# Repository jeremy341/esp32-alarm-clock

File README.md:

# ESP32-S3 Alarm Clock

Custom alarm clock built around an `ESP32-S3-WROOM-1` on a dedicated PCB, with an `ILI9341` display, battery powerer , Website , and USB C for both flashing and charging. The website allows the user to choose from existing presets and change the color of them, to change the UI.
I created this Project as a birthday gift for my little sister as in the morning i always wake her up and she doesnt have a alarm, I also wanted to gain new skills as i want to become an enginier and build up my CV.

## Overview

- `ESP32-S3-WROOM-1`
- `ILI9341` SPI display
- `IP5306` power-path, Li-ion charge, and boost stage
- `LV75533PDBVR` 3.3 V regulator
- `USBLC6-2SC6` USB ESD protection
- `2N3904` transistor-driven buzzer stage with `1N4148`
- `LittleFS` storage for presets and alarms
- `WebSerial` browser app for preset upload

## IMAGES

## Hardware

| Block | Part | Role |
|---|---|---|
| MCU | `ESP32-S3-WROOM-1` | Main control, USB serial, UI logic |
| Display | `ILI9341` | TFT clock UI |
| USB | USB-C receptacle | Power + USB data |
| ESD | `USBLC6-2SC6` | Protection for `D+` / `D-` |
| Power manager | `IP5306` | Li-ion charging and 5 V boost |
| 3.3 V rail | `LV75533PDBVR` | Logic supply for ESP32-S3 and display |
| Audio driver | `2N3904` + `1N4148` | GPIO-switched buzzer stage |
| Storage | `LittleFS` | Preset and alarm persistence |

## Power Path

```text
USB-C VBUS
  -> IP5306
     -> Li-ion charging
     -> 5V_SYS
        -> LV75533PDBVR
           -> 3.3V rail
              -> ESP32-S3 + ILI9341 + logic
```

## Pin Map

### ILI9341

| Signal | GPIO |
|---|---|
| `SCK` | `GPIO12` |
| `MOSI` | `GPIO11` |
| `MISO` | `GPIO13` |
| `CS` | `GPIO10` |
| `DC` | `GPIO9` |
| `RST` | `GPIO14` |
| `GND` | `GND` |
| `VCC` | `3.3V` |

### Buttons

| Function | GPIO | Notes |
|---|---|---|
| `RESET` | `EN` | Active low |
| `BOOT` | `GPIO0` | Hold low during reset for flash mode |
| `MENU` | `GPIO1` | `INPUT_PULLUP`, switch to GND |
| `UP` | `GPIO2` | `INPUT_PULLUP`, switch to GND |
| `DOWN` | `GPIO5` | `INPUT_PULLUP`, switch to GND |

### Other PINS

| Signal | GPIO | Notes |
|---|---|---|
| `BUZZER` | `GPIO4` | Drives transistor stage |
| `USB D-` | `GPIO19` | USB only |
| `USB D+` | `GPIO20` | USB only |

## Web App

The browser app is served from `web/` and is intended for Chrome or firefox, browsers with WebSerial support. Its function is choosing of custom ui and flashing `ESP32`.

## Getting Started

```bash
cd firmware
pio run
pio run -t upload
pio run -t uploadfs
```

```bash
cd web
python -m http.server 8000
```

Then open [http://localhost:8000](http://localhost:8000) in Chrome or Edge.

## Bill of Materials (BOM)

| Part Name | Distributor | Qty | LCSC Part # / Spec | Link | Price |
| :--- | :--- | :--- | :--- | :--- | :--- |
| **ESP32-S3-WROOM-1** | LCSC | 1 | C2913202 | [Link](https://www.lcsc.com/product-detail/C2913202.html) | $4.95 |
| **IP5306** | LCSC | 1 | C181552 | [Link](https://www.lcsc.com/product-detail/C181552.html) | $3.95 |
| **ILI9341 Display** | Aliexpress | 1 | 2.8" SPI TFT | [Link](https://de.aliexpress.com/item/1005009761383945.html) | $5.79 |
| **3000 mAh LiPo Battery** | Aliexpress | 1 | 3.7V Cell | [Link](https://de.aliexpress.com/item/1005009240348340.html) | $14.99 |
| **Custom PCB** | JLCPCB | 1 | 2-Layer FR4 | [Link](https://jlcpcb.com/) | $6.40 |
| **Mechanical Switch (UP)** | Aliexpress | 1 | Gateron/Akko Style | [Link](https://de.aliexpress.com/item/1005011838889689.html) | $0.00* |
| **Mechanical Switch (DOWN)** | Aliexpress | 1 | Gateron/Akko Style | [Link](https://de.aliexpress.com/item/1005011838889689.html) | $2.73 |
| **Mechanical Switch (Menu)** | Aliexpress | 1 | Gateron/Akko Style | [Link](https://de.aliexpress.com/item/1005011838889689.html) | $0.00* |
| **TLV75533PDBV** | LCSC | 1 | C404027 | [Link](https://www.lcsc.com/product-detail/C404027.html) | $0.62 |
| **USBLC6-2SC6** | LCSC | 1 | C7519 | [Link](https://www.lcsc.com/product-detail/C7519.html) | $0.76 |
| **USB-C Port (16P)** | LCSC | 1 | C165948 | [Link](https://www.lcsc.com/product-detail/C165948.html) | $0.85 |
| **Passive Buzzer** | LCSC | 1 | C409842 | [Link](https://www.lcsc.com/product-detail/C409842.html) | $0.71 |
| **Battery Connector** | LCSC | 1 | C22360303 | [Link](https://www.lcsc.com/product-detail/C22360303.html) | $0.35 |
| **2N3904 Transistor** | LCSC | 1 | C2874602 | [Link](https://www.lcsc.com/product-detail/C2874602.html) | $0.54 |
| **1N4148 Diode** | LCSC | 1 | C85057 | [Link](https://www.lcsc.com/product-detail/C85057.html) | $0.62 |
| **2.2 µH Inductor** | LCSC | 1 | C7427099 | [Link](https://www.lcsc.com/product-detail/C7427099.html) | $0.40 |
| **100nF Capacitor** | LCSC | 1 | C49678 | [Link](https://www.lcsc.com/product-detail/C49678.html) | $0.53 |
| **10uF Capacitor** | LCSC | 5 | C15850 | [Link](https://www.lcsc.com/product-detail/C15850.html) | $0.41 |
| **1uF Capacitor** | LCSC | 1 | C28323 | [Link](https://www.lcsc.com/product-detail/C28323.html) | $0.28 |
| **5.1K Resistor** | LCSC | 2 | C714010 | [Link](https://www.lcsc.com/product-detail/C714010.html) | $0.74 |
| **22Ω Resistor** | LCSC | 2 | C3009224 | [Link](https://www.lcsc.com/product-detail/C3009224.html) | $0.41 |
| **1k Resistor** | LCSC | 1 | C713997 | [Link](https://www.lcsc.com/product-detail/C713997.html) | $0.77 |
| **10K Resistor** | LCSC | 2 | C119347 | [Link](https://www.lcsc.com/product-detail/C119347.html) | $0.56 |
| **System Button (BOOT)** | LCSC | 1 | C42416254 | [Link](https://www.lcsc.com/product-detail/C42416254.html) | $1.46 |
| **System Button (RESET)** | LCSC | 1 | C42416254 | [Link](https://www.lcsc.com/product-detail/C42416254.html) | $0.00* |
| **System Button (KEY)** | LCSC | 1 | C42416254 | [Link](https://www.lcsc.com/product-detail/C42416254.html) | $0.00* |

*\*Note: 1 often just shows the minimum quantity availaiable so its just the minimum included in a single pack price, also the $0.00 are duplicates so they are alredy included in the pack of similar items such as the buttons.*

This Project was aided by Ai in the communication between the firmware and the webserial and the creation of the webapp, the rest is self written.

## License

This project is licensed under the **MIT License**. This means you are free to use, modify, and distribute the software and hardware designs, as long as you include the original copyright notice. 

See the [LICENSE](LICENSE) file for the full text.

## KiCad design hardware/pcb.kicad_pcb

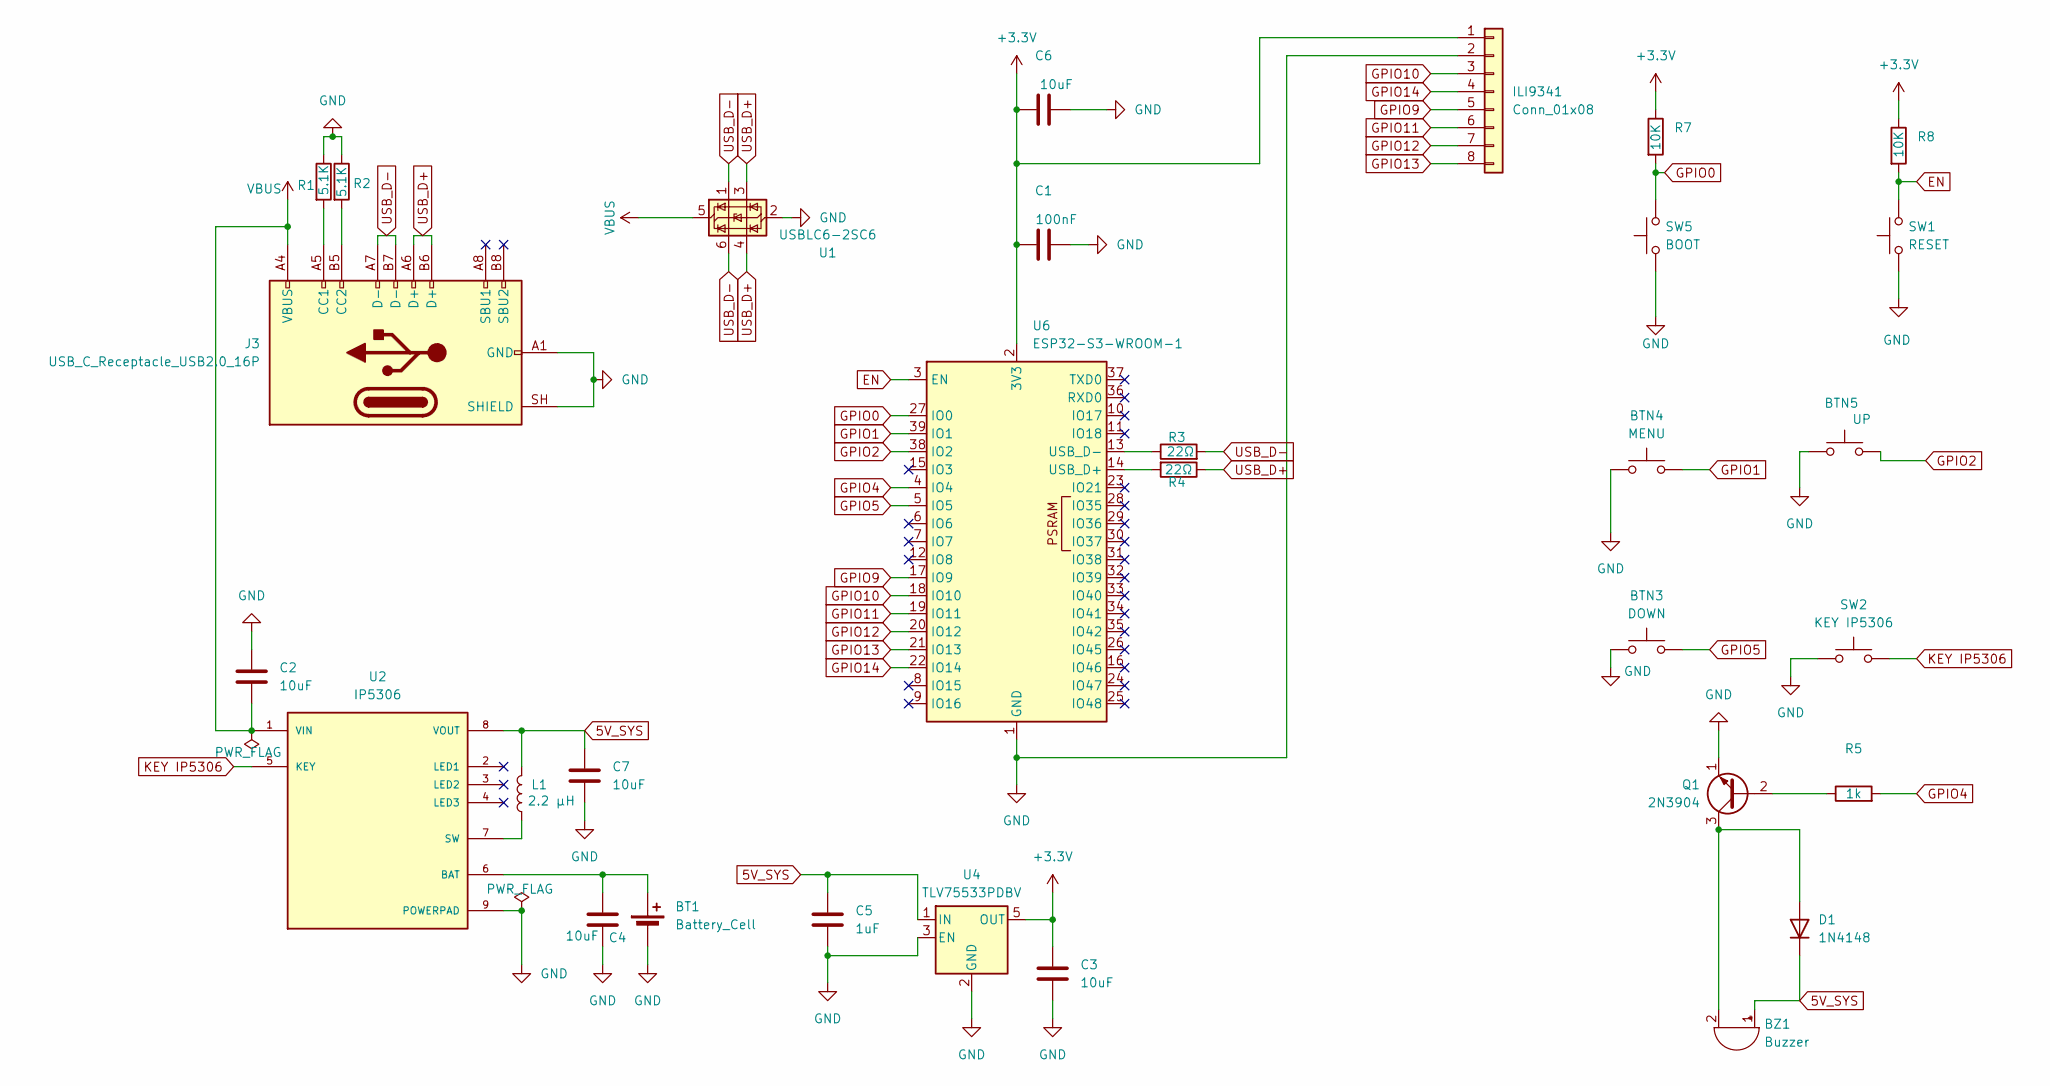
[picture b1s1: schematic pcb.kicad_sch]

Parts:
BT1: Battery_Cell; JST_PH_S2B-PH-K_1x02_P2.00mm_Horizontal
BTN3: DOWN; PinHeader_1x02_P2.54mm_Vertical
BTN4: MENU; PinHeader_1x02_P2.54mm_Vertical
BTN5: UP; PinHeader_1x02_P2.54mm_Vertical
BZ1: Buzzer; Buzzer_12x9.5RM7.6
C1: 100nF; C_0805_2012Metric; LCSC C49678
C2, C3, C4, C6, C7: 10uF; C_0805_2012Metric; LCSC C15850
C5: 1uF; C_0805_2012Metric; LCSC C28323
D1: 1N4148; D_DO-35_SOD27_P7.62mm_Horizontal
ILI9341: Conn_01x08; PinHeader_1x08_P2.54mm_Vertical
J3: USB_C_Receptacle_USB2.0_16P; USB_C_Receptacle_GCT_USB4110; LCSC C165948
L1: 2.2 µH; L_APV_ANR4018; LCSC C408298
Q1: 2N3904; TO-92_Inline
R1, R2: 5.1K; R_Axial_DIN0207_L6.3mm_D2.5mm_P7.62mm_Horizontal
R3, R4: 22Ω; R_Axial_DIN0207_L6.3mm_D2.5mm_P7.62mm_Horizontal
R5: 1k; R_Axial_DIN0207_L6.3mm_D2.5mm_P7.62mm_Horizontal
R7, R8: 10K; R_Axial_DIN0207_L6.3mm_D2.5mm_P7.62mm_Horizontal
SW1: RESET; SW_PUSH_6mm_H4.3mm
SW2: KEY IP5306; SW_PUSH_6mm_H4.3mm
SW5: BOOT; SW_PUSH_6mm_H4.3mm
U1: USBLC6-2SC6; SOT-23-6; LCSC C7519
U2: IP5306; SOP127P600X165-9N; PARTREV 1.31; LCSC C181552
U4: TLV75533PDBV; SOT-23-5; LCSC C263071
U6: ESP32-S3-WROOM-1; LCSC C2913202

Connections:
5V_SYS: BZ1.1 (+), C5.1, C7.1, D1.1 (K), L1.2, U2.8 (VOUT), U4.1 (IN)
+3.3V: C1.1, C3.1, C6.1, ILI9341.1, R7.1, R8.1, U4.5 (OUT), U6.2 (3V3)
EN: R8.2, SW1.2, U6.3 (EN)
GND: BT1.2 (-), BTN3.1, BTN4.1, BTN5.1, C1.2, C2.1, C3.2, C4.2, C5.2, C6.2, C7.2, ILI9341.2, J3.A1 (GND), J3.A12 (GND), J3.B1 (GND), J3.B12 (GND), J3.SH (SHIELD), Q1.1 (E), R1.1, R2.1, SW1.1, SW2.1, SW5.1, U1.2 (GND), U2.9 (POWERPAD), U4.2 (GND), U4.3 (EN), U6.1 (GND), U6.40 (GND), U6.41 (GND)
GPIO0: R7.2, SW5.2, U6.27 (IO0)
GPIO1: BTN4.2, U6.39 (IO1)
GPIO2: BTN5.2, U6.38 (IO2)
GPIO4: R5.2, U6.4 (IO4)
GPIO5: BTN3.2, U6.5 (IO5)
GPIO9: ILI9341.5, U6.17 (IO9)
GPIO10: ILI9341.3, U6.18 (IO10)
GPIO11: ILI9341.6, U6.19 (IO11)
GPIO12: ILI9341.7, U6.20 (IO12)
GPIO13: ILI9341.8, U6.21 (IO13)
GPIO14: ILI9341.4, U6.22 (IO14)
KEY IP5306: SW2.2, U2.5 (KEY)
unnamed: BT1.1 (+), C4.1, U2.6 (BAT)
unnamed: BZ1.2 (-), D1.2 (A), Q1.3 (C)
unnamed: J3.A5 (CC1), R1.2
unnamed: J3.B5 (CC2), R2.2
unnamed: Q1.2 (B), R5.1
unnamed: L1.1, U2.7 (SW)
unnamed: R4.2, U6.14 (USB_D+)
unnamed: R3.1, U6.13 (USB_D-)
USB_D+: J3.A6 (D+), J3.B6 (D+), R4.1, U1.3 (I/O2), U1.4 (I/O2)
USB_D-: J3.A7 (D-), J3.B7 (D-), R3.2, U1.1 (I/O1), U1.6 (I/O1)
VBUS: C2.2, J3.A4 (VBUS), J3.A9 (VBUS), J3.B4 (VBUS), J3.B9 (VBUS), U1.5 (VBUS), U2.1 (VIN)

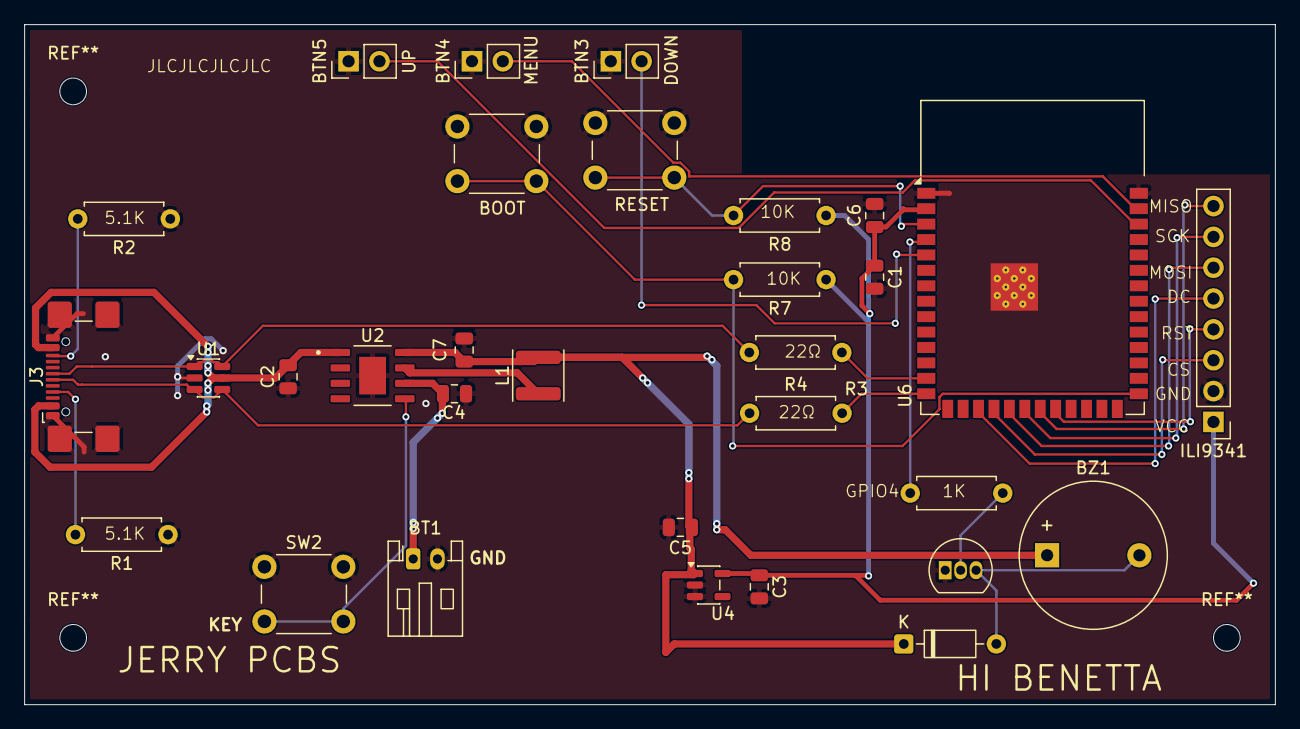
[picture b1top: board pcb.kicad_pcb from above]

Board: 4 copper layers, 103.0 x 56.0 mm, 31 parts (0 on the bottom side), 27 nets.

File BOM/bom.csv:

Part Name,Distrubutor,Quantity,LCSC Part ,Link,Price
Battery_Cell,LCSC ,1,C22360303,https://www.lcsc.com/product-detail/C22360303.html?spm=wm.gw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,0.35$ 
DOWN,Aliexpress,1,,https://de.aliexpress.com/item/1005011838889689.html?spm=a2g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,2.73$ 
Menu,Aliexpress,1,,https://de.aliexpress.com/item/1005011838889689.html?spm=a2g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,0.00$ 
UP,Aliexpress,1,,https://de.aliexpress.com/item/1005011838889689.html?spm=a2g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,0.00$ 
Buzzer,LCSC ,1,C409842,https://www.lcsc.com/product-detail/C409842.html?spm=wm.gwc.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,0.71$ 
100nF,LCSC ,1,C49678,https://www.lcsc.com/product-detail/C49678.html?spm=wm.gwc.x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,0.53$ 
10uF,LCSC ,5,C15850 ,https://www.lcsc.com/product-detail/C15850.html?spm=wm.gwc.d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,0.41$ 
1uF,LCSC ,1,C28323,https://www.lcsc.com/product-detail/C28323.html?spm=wm.gwc.d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,0.28$ 
1N4148,LCSC ,1,C85057 ,https://www.lcsc.com/product-detail/C85057.html?spm=wm.gwc.x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,0.62$ 
ILI9341,Aliexpress,1,,https://de.aliexpress.com/item/1005009761383945.html?spm=a2g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,5.79$ 
USB_C_Receptacle_USB2.0_16P,LCSC ,1,C165948,https://www.lcsc.com/product-detail/C165948.html?spm=wm.gwc.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,0.85$ 
2.2 µH,LCSC ,1,C7427099 ,https://www.lcsc.com/product-detail/C7427099.html?spm=wm.gwc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,0.40$ 
2N3904,LCSC ,1,C2874602 ,https://www.lcsc.com/product-detail/C2874602.html?spm=wm.gwc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,0.54$ 
5.1K,LCSC ,1,C714010,https://www.lcsc.com/product-detail/C714010.html?spm=wm.gwc.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,0.74 $ 
22Ω,LCSC ,1,C3009224,https://www.lcsc.com/product-detail/C3009224.html?spm=wm.gwc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,0.41 $ 
1k,LCSC ,1,C713997,https://www.lcsc.com/product-detail/C713997.html?spm=wm.gwc.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,0.77 $ 
10K,LCSC ,2,C119347,https://www.lcsc.com/product-detail/C119347.html?spm=wm.gwc.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,0.56 $ 
RESET,LCSC ,1,C42416254,https://www.lcsc.com/product-detail/C42416254.html?spm=wm.gw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,0.00 $ 
KEY IP5306,LCSC ,1,C42416254,https://www.lcsc.com/product-detail/C42416254.html?spm=wm.gw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,0.00 $ 
BOOT,LCSC ,1,C42416254,https://www.lcsc.com/product-detail/C42416254.html?spm=wm.gw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,1.46 $ 
USBLC6-2SC6,LCSC ,1,C7519,https://www.lcsc.com/product-detail/C7519.html?spm=wm.gwc.xh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,0.76 $ 
IP5306,LCSC ,1,C181552,https://www.lcsc.com/product-detail/C181552.html?spm=wm.gwc.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,3.95 $ 
TLV75533PDBV,LCSC ,1,C404027 ,https://www.lcsc.com/product-detail/C404027.html?spm=wm.gwc.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,0.62 $ 
ESP32-S3-WROOM-1,LCSC ,1,C2913202,https://www.lcsc.com/product-detail/C2913202.html?spm=wm.gwc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,4.95 $ 
 3000 mAh Lipo-Batterie  ,Aliexpress,1,,https://de.aliexpress.com/item/1005009240348340.html?spm=a2g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,14.99$ 
Custom PCB,JLC PCB,1,,,"6,40$ "

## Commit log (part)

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2026-04-15 initial project structure
2026-04-15 initial modular ESP32 bitmap system
2026-04-15 restructure project + initial ESP32 bitmap system
2026-04-15 initial architecture: esp32 alarm clock system
2026-04-16 fixed layout system + geometry bug
2026-04-17 Updated web UI
2026-04-17 Fix preset field name in README to clockStyle
2026-04-18 Update README with correct pin mappings and web theme button functionality
2026-04-18 Update layout, alarm UI, and web carousel
2026-04-30 Update README and custom PCB pin map
2026-05-05 Align custom PCB pins and clean firmware protocol
2026-05-09 Revise README with project details and images
2026-05-09 Upload of schematic
2026-05-09 Upload of the PCB renderd
2026-05-09 Upload of missing images
2026-05-09 All cad files
2026-05-09 Gerber file of PCB
2026-05-09 Created the Bom
2026-05-09 All pcb files
2026-05-10 Addes BOM and fixed typos and pictures
2026-05-10 Add MIT License to the project
2026-05-10 Fix formatting of 'WebSerial' in README.md
2026-06-01 Document AI contribution in project README
    Added note about AI assistance in project development.
2026-06-03 Updated PCB fixed USB C facing inwards the board
2026-06-04 Create test
2026-06-04 Move file into PCB folder
2026-06-04 Addes Stl files for the project
2026-06-04 Update project description in README.md
    Clarified the contribution of AI in the project description.
